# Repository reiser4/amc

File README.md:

# amc

Software utilizzato su Windows:

 Python 3.5.0
 https://www.python.org/ftp/python/3.5.0/python-3.5.0-amd64-webinstall.exe

 PyQt5 5.5
 http://sourceforge.net/projects/pyqt/files/PyQt5/PyQt-5.5/PyQt5-5.5-gpl-Py3.4-Qt5.5.0-x64.exe

 py2exe 0.9.2.0
 https://pypi.python.org/packages/any/p/py2exe/py2exe-0.9.2.0.win-amd64.exe#md5=05d90513c993b2f3ae0f7f21d69a6898

Per compilare per windows:

 python setup.py py2exe --includes sip

# funzionamento

il software AMC gira su beaglebone black. E` costituito da diversi componenti che interagiscono tra loro solamente tramite lettura e scrittura (atomica) di files in /tmp.

/tmp/band.txt
	contiene la banda in uso. puo` essere: 160, 80, 60, 40, 30, 20, 17, 15, 12, 10, 6

/tmp/relay.txt
	descrive i rele` attivi con la combinazione attuale di preset.
	esempio: 100000000000000000000000
	nella nostra implementazione usiamo i primi otto bits

/tmp/presetA.txt e /tmp/presetB.txt
	descrivono la combinazione da tastiera scelta dall'utente
	la pressione dei tasti provoca la variazione della combinazione
	esempio:
		TX: 01100000
		RX: 10010000

/tmp/presetTXTA.txt e /tmp/presetTXTB.txt
	contiene la lista testuale di preset attivi (per essere stampato sul display)
	senza spazi, separati da virgola, poi punto e virgola tra Rx e Tx
	esempio:
		Europa,Asia,America;Asia

/tmp/tx.txt
	contiene la lista di radio che stanno trasmettendo in quel momento
	esempio:
		A
		oppure
		B
		oppure 
		(file vuoto)

/root/amc/config.json
	contiene la configurazione con cui vengono determinate le varie combinazioni di relay da accendere.
	vedi file di esempio

# componenti software

MAIN:
	si occupa di prendere le decisioni riguardo i preset e relay da attivare.
	LEGGE: /root/amc/config.json /tmp/tx.txt /tmp/presetA.txt /tmp/presetB.txt /tmp/band.txt
	SCRIVE: /tmp/relay.txt /tmp/presetTXTA.txt /tmp/presetTXTB.txt

IOLOOP:
	ascolta il GPIO hardware per determinare la banda e la radio trasmittente.
	SCRIVE: /tmp/band.txt /tmp/tx.txt

DISPLAY:
	si occupa di mantenere il display aggiornato con lo stato attuale.
	LEGGE: /tmp/tx.txt /tmp/band.txt /tmp/presetTXTA.txt /tmp/presetTXTB.txt

KEYBOARD:
	rimane in ascolto di input da tastiera e fa i toggle dei bits dei preset
	LEGGE: /tmp/presetA.txt /tmp/presetB.txt
	SCRIVE: /tmp/presetA.txt /tmp/presetB.txt

SERIAL:
	svolge due funzioni: riporta periodicamente sulla seriale lo stato attuale per poter essere visualizzato sul pc,
	ed interagisce col pc per inviare e ricevere la configurazione.
	LEGGE: /tmp/presetA.txt /tmp/presetB.txt /tmp/tx.txt /tmp/band.txt /tmp/presetTXTA.txt /tmp/presetTXTB.txt /root/amc/config.json
	SCRIVE: /root/amc/config.json

RELAY:
	scrive su GPIO le uscite relay
	LEGGE: /tmp/relay.txt

CHECK:
	verifica che tutti i processi siano in esecuzione ed avvia eventuali processi fermi.

===================================

Requisiti software

# apt-get install git
# pip install Pillow

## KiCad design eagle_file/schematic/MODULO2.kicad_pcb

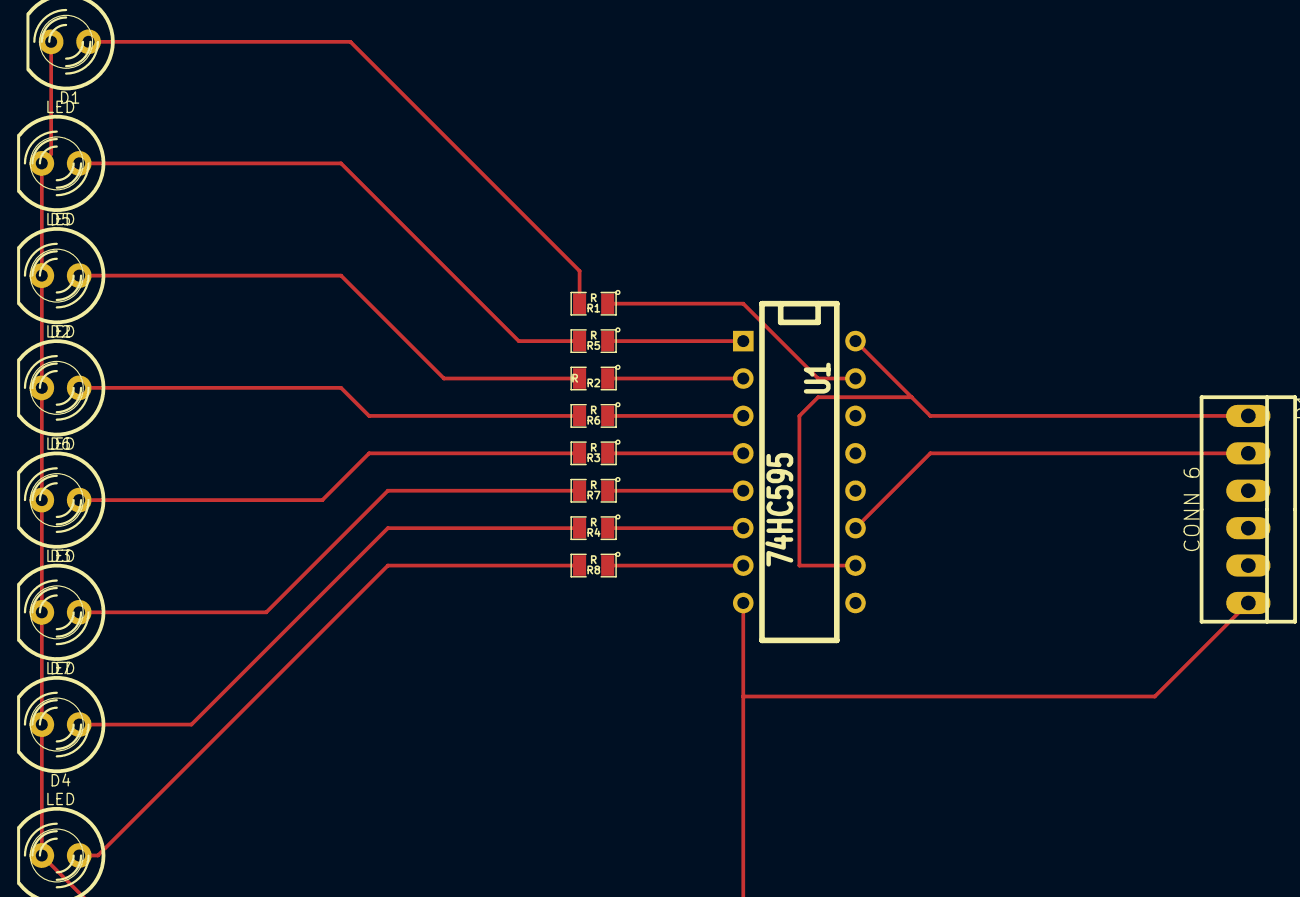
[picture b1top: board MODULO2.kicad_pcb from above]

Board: 2 copper layers, 18 parts (0 on the bottom side), 22 nets.

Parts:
D1, D2, D3, D4, D5, D6, D7, D8: LED; LED-5MM
P1: CONN_6; PINHEAD1-6
R1, R2, R3, R4, R5, R6, R7, R8: R; SM0805
U1: 74HC595; DIP-16__300

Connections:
/SCLK: P1.2, U1.11
GND: D1.2, D2.2, D3.2, D4.2, D5.2, D6.2, D7.2, D8.2, P1.6, U1.8, U1.13
unnamed: R4.1, U1.6
unnamed: D7.1, R7.2
unnamed: R7.1, U1.5
unnamed: D3.1, R3.2
unnamed: R3.1, U1.4
unnamed: D4.1, R4.2
unnamed: D6.1, R6.2
unnamed: R6.1, U1.3
unnamed: D2.1, R2.2
unnamed: R2.1, U1.2
unnamed: D5.1, R5.2
unnamed: R5.1, U1.1
unnamed: D8.1, R8.2
unnamed: R8.1, U1.7
unnamed: R1.1, U1.15
unnamed: P1.3, U1.14
unnamed: P1.5, U1.12
unnamed: D1.1, R1.2
unnamed: P1.4, U1.9
VCC: P1.1, U1.10, U1.16

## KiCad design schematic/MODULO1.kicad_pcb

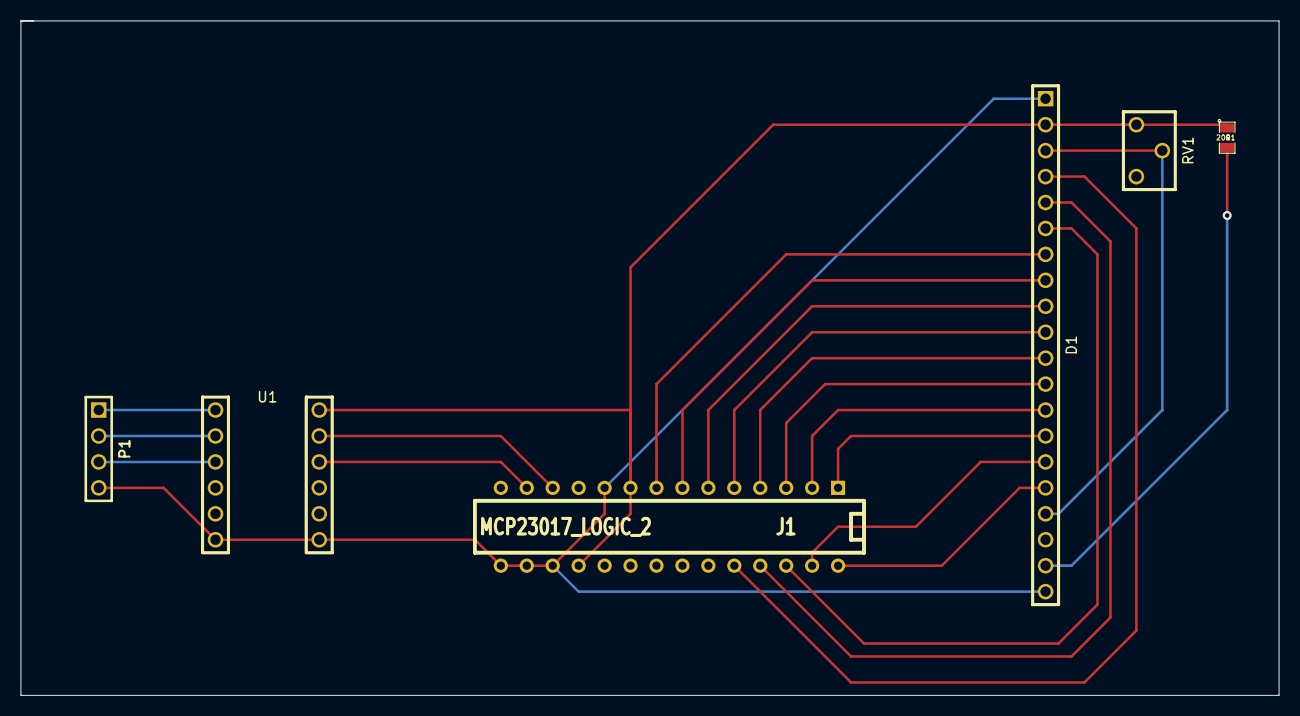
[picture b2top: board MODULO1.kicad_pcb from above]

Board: 2 copper layers, 123.2 x 66.0 mm, 6 parts (0 on the bottom side), 22 nets.

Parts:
D1: RG16080B-BIY-V_LOGIC_2; ZZPIN20
J1: MCP23017_LOGIC_2; DIP-28__300
P1: CONN_4; PIN_ARRAY_4x1
R1: 200; SM0805
RV1: POT; ZZTRIMMER
U1: L_CONVERTER

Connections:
/SCL: P1.2, U1.2
/SDA: P1.3, U1.3
GND: D1.1, D1.20, J1.10, J1.15, J1.16, J1.17, P1.4, U1.6, U1.7
unnamed: J1.13, U1.10
unnamed: D1.12, J1.3
unnamed: D1.13, J1.2
unnamed: D1.11, J1.4
unnamed: D1.10, J1.5
unnamed: D1.9, J1.6
unnamed: D1.8, J1.7
unnamed: D1.7, J1.8
unnamed: D1.5, J1.25
unnamed: D1.2, J1.9, J1.18, R1.1, RV1.1, U1.12
unnamed: D1.4, J1.24
unnamed: D1.6, J1.26
unnamed: D1.15, J1.27
unnamed: D1.16, J1.28
unnamed: D1.3, D1.17, RV1.2
unnamed: J1.12, U1.11
unnamed: D1.19, R1.2
unnamed: D1.14, J1.1
VCC: P1.1, U1.1

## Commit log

2015-04-14 commit iniziale
2015-04-14 rename
2015-04-14 test
2015-04-14 first-one-wins logic
2015-04-14 double = missing
2015-04-14 init and read radio ptt
2015-04-14 pin settings
2015-04-14 ptt logic
2015-04-14 debug
2015-04-20 configuration sample
2015-04-21 bcd picture
2015-04-21 web page
2015-04-21 prova
2015-04-21 web fix
2015-04-21 web page fix
2015-04-22 modifica read input xkeys
2015-04-22 front webpage
2015-04-22 aggiunti led sul frontale
2015-04-22 front simulator
2015-04-22 relay output
2015-04-24 relay visual output improved
2015-04-24 gitignore update
2015-04-24 creata classe per leggere da tastiera
2015-04-27 Schematic
2015-04-27 verbose text disabled; dxlog band decoder
2015-04-27 relay fix
2015-04-28 display beginning
2015-04-28 new class 'atomicwrite'
2015-04-29 keyboard as radio button, atomic front, cape
2015-04-29 add functions to writeRect and writeLine
2015-04-29 bug fix keyboardxkeys.py
2015-05-03 font and a few test
2015-05-07 Schema di base
2015-05-07 Collegato alla 5V
2015-05-18 display driver working
2015-05-24 configuration panel test
2015-05-24 ricarico il file dxlog-band.py che nelle precedente commit ho cancellato
2015-05-26 aggiunta di commenti al file configuration-panel.py
2015-05-28 Schematico Logico
2015-06-01 Revert "Merge branch 'master' of https://github.com/reiser4/amc"
    This reverts commit 2380cc5f35dc9174c4fa96b8073f98d69a9940f7, reversing
    changes made to 8732c452cd3d8e44b63f819e5c39efa00f12953a.
2015-06-01 Revert "Revert "Merge branch 'master' of https://github.com/reiser4/amc""
    This reverts commit 9bf984cd97639c6bb09fb1a1b6d99ebaa172ac6a.
2015-06-01 Fix typos and default settings and state
2015-06-01 Working on printing text on display
2015-06-02 configuration panel row and column decode
2015-06-20 now configuration-panel.py can save configuration
2015-06-20 fix bug for save configuration
2015-06-21 now configuration-panel.py can load configuration
2015-06-21 add toolbar, icons for save and load configuration
2015-06-28 rinomino i file per seguire le linee guida di PEP8
2015-07-15 adesso possiamo decidere il nome del file da salvare
2015-07-23 status to serial port
2015-07-23 got display
2015-07-23 work on display
2015-07-23 display cycle sleep
2015-07-29 Eagle File
    Schematics made in Eagle
2015-07-29 GND to MODULO0
    Ho messo a massa il Modulo0
2015-07-29 Modulo0 pdf
    Come da titolo
2015-07-29 Modulo 0 pdf
    Modulo 0 senza contorno ai fori
2015-07-29 Fix Modulo 0
    Pin all'esterno della scheda
2015-07-30 Modulo 2_2 pdf
2015-07-30 Modulo 2_1
    Modolo2_1.pdf per controllare i footprint
2015-07-30 MODULO2_def
2015-07-30 PDF Vari
    Ecco Tutti i pdf
2015-07-31 Fix PDF
    Ho tolto alcuni layer inutili dal pdf dei PCB
2015-08-05 viewpanel.py alpha
2015-08-07 viewpanel.py beta
2015-08-07 aggiunta la possibilità di fare l'upload della configurazione sul beaglebone in configpanel.py
2015-08-08 use os.path for the icons
2015-09-03 Divisione di modulo 2
2015-09-04 pdf MODULO2
2015-09-08 gerbers
2015-09-08 MODULO2_OLD
2015-09-10 Modulo1
2015-09-10 Modulo1 greber
2015-09-10 Modulo0
2015-09-11 Modulo2
2015-09-29 exe standalone
2015-09-29 readme
2015-10-15 Modulo ShiftRegister
    Aggiunto il modulo ShiftRegister, scritto con pseudocodice.
2015-10-16 shift register working
2015-10-26 new readme. shiftregister
2015-10-26 riorganizzazione file
2015-10-26 moved shiftregister
2015-10-26 relay now working
2015-10-26 relay complete
2015-10-26 relay is now foolproof
2015-10-26 display almost finished and almost foolproof
2015-10-26 keyboard OK for 1 keyboard
2015-10-26 display shows preset A
2015-10-27 moved files around
2015-10-27 python2 to python3...
2015-10-27 view panel working
2015-10-29 display driver in C
2015-11-01 corretti alcuni errori del viewpanel
2015-11-01 corretti alcuni errori nel configpanel
2015-11-03 run script
2015-11-03 serial renamed
2015-11-03 cosmetics
2015-11-04 serial upload working
2015-11-06 aggiunta possibilità di download e upload configurazione nel configpanel
2015-11-06 upload working
2015-11-06 download working
2015-11-06 current conf. upload almost working
2015-11-06 saving config only before upload
2015-11-06 fix per spazi
2016-06-21 prima di reindent
2016-08-05 requisiti
2016-08-15 lavori su main per versione finale
2016-08-15 relay ok!!!!!
2017-08-07 letta banda da piedini giusti; scrittura display su file; fix tastiere
